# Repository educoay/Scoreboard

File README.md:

# Scoreboard
Arduino powered scoreboard with wired controller

**The wireless branch is newer and currently used in the application**

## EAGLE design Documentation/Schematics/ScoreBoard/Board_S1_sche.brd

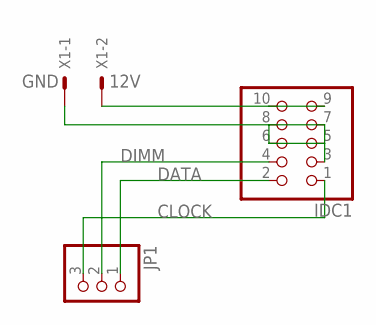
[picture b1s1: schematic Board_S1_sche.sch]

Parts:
IDC1: PINHD-2X5; 2X05
JP1: PINHD-1X3; 1X03
X1: KK-156-2

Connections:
12V: IDC1.9, IDC1.10, X1.2
CLOCK: IDC1.1, JP1.3
DATA: IDC1.2, JP1.1
DIMM: IDC1.4, JP1.2
GND: IDC1.3, IDC1.5, IDC1.6, IDC1.7, IDC1.8, X1.1

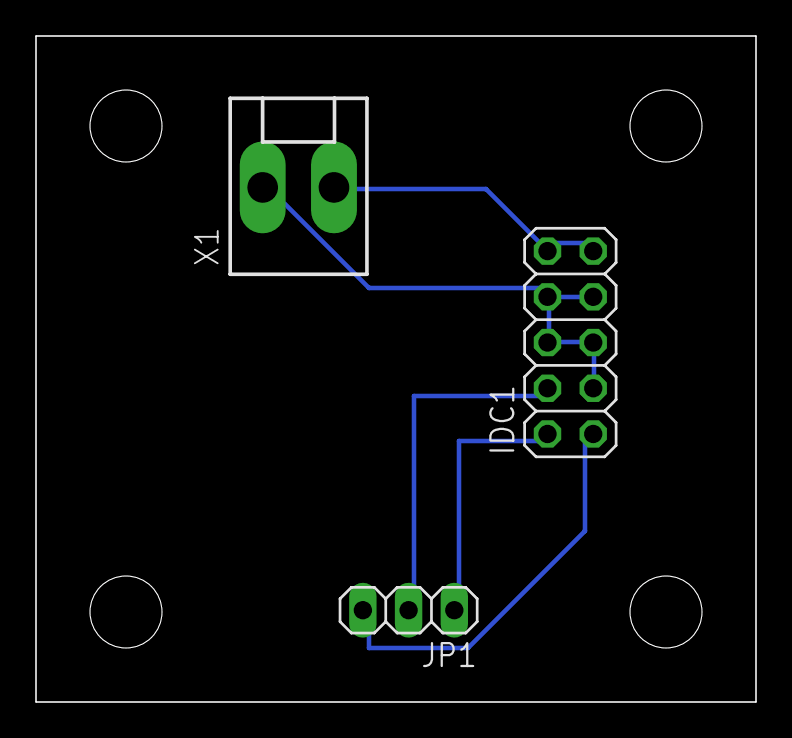
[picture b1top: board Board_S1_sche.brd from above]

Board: 2 copper layers, 40.0 x 37.0 mm, 3 parts (0 on the bottom side), 5 nets.

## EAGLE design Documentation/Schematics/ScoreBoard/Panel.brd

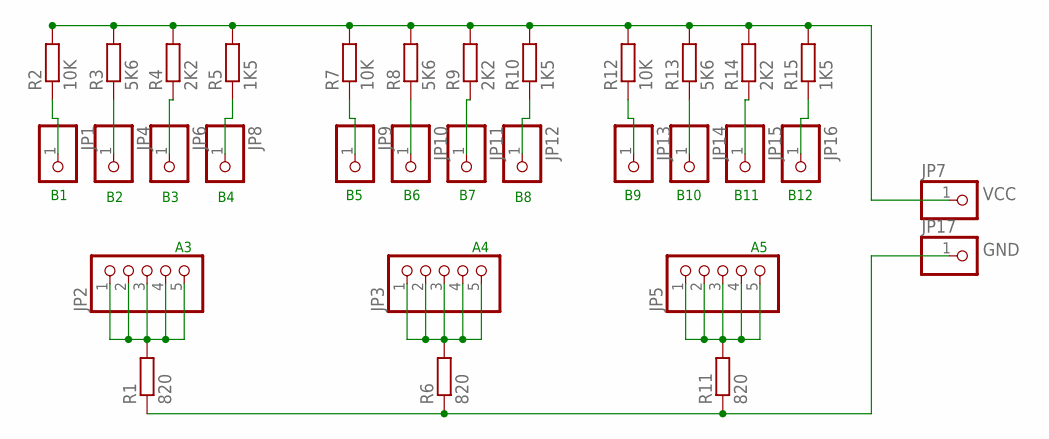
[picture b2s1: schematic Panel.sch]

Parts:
JP1, JP4, JP6, JP7, JP8, JP9, JP10, JP11, JP12, JP13, JP14, JP15, JP16, JP17: PINHD-1X1; 1X01
JP2, JP3, JP5: PINHD-1X5; 1X05
R1, R6, R11: 820; 0207/12
R2, R7, R12: 10K; 0207/12
R3, R8, R13: 5K6; 0207/12
R4, R9, R14: 2K2; 0207/12
R5, R10, R15: 1K5; 0207/12

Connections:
A1: JP3.1, JP3.2, JP3.3, JP3.4, JP3.5, R6.2
A2: JP5.1, JP5.2, JP5.3, JP5.4, JP5.5, R11.2
A3: JP2.1, JP2.2, JP2.3, JP2.4, JP2.5, R1.2
B1: JP1.1, R2.1
B2: JP4.1, R3.1
B3: JP6.1, R4.1
B4: JP8.1, R5.1
B5: JP9.1, R7.1
B6: JP10.1, R8.1
B7: JP11.1, R9.1
B8: JP12.1, R10.1
B9: JP13.1, R12.1
B10: JP14.1, R13.1
B11: JP15.1, R14.1
B12: JP16.1, R15.1
GND: JP17.1, R1.1, R6.1, R11.1
VCC: JP7.1, R2.2, R3.2, R4.2, R5.2, R7.2, R8.2, R9.2, R10.2, R12.2, R13.2, R14.2, R15.2

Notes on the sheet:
B10
B11
B12

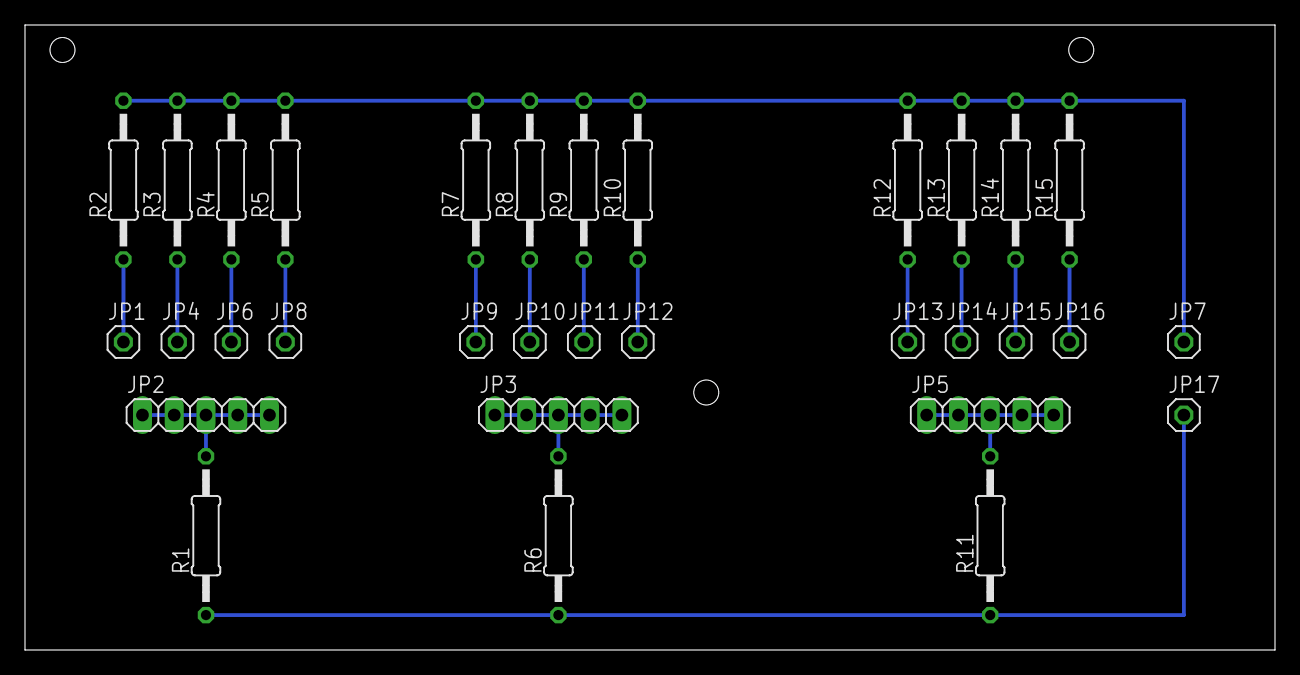
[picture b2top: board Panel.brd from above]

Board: 2 copper layers, 100.0 x 50.0 mm, 32 parts (0 on the bottom side), 17 nets.

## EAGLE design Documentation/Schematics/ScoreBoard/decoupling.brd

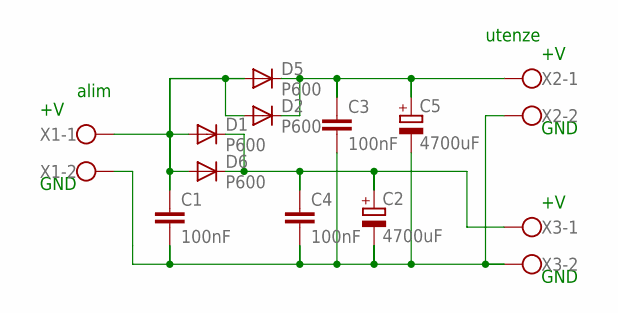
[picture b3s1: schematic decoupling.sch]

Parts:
C1, C3, C4: 100nF; C050-025X075
C2, C5: 4700uF; E7,5-16
D1, D2, D5, D6: P600; P6-15
X1, X2, X3: W237-102

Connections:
unnamed: C1.2, C2.-, C3.2, C4.2, C5.-, X1.2, X2.2, X3.2
unnamed: C1.1, D1.A, D2.A, D5.A, D6.A, X1.1
unnamed: C2.+, C4.1, D1.C, D6.C, X3.1
unnamed: C3.1, C5.+, D2.C, D5.C, X2.1

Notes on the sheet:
alim
utenze
GND

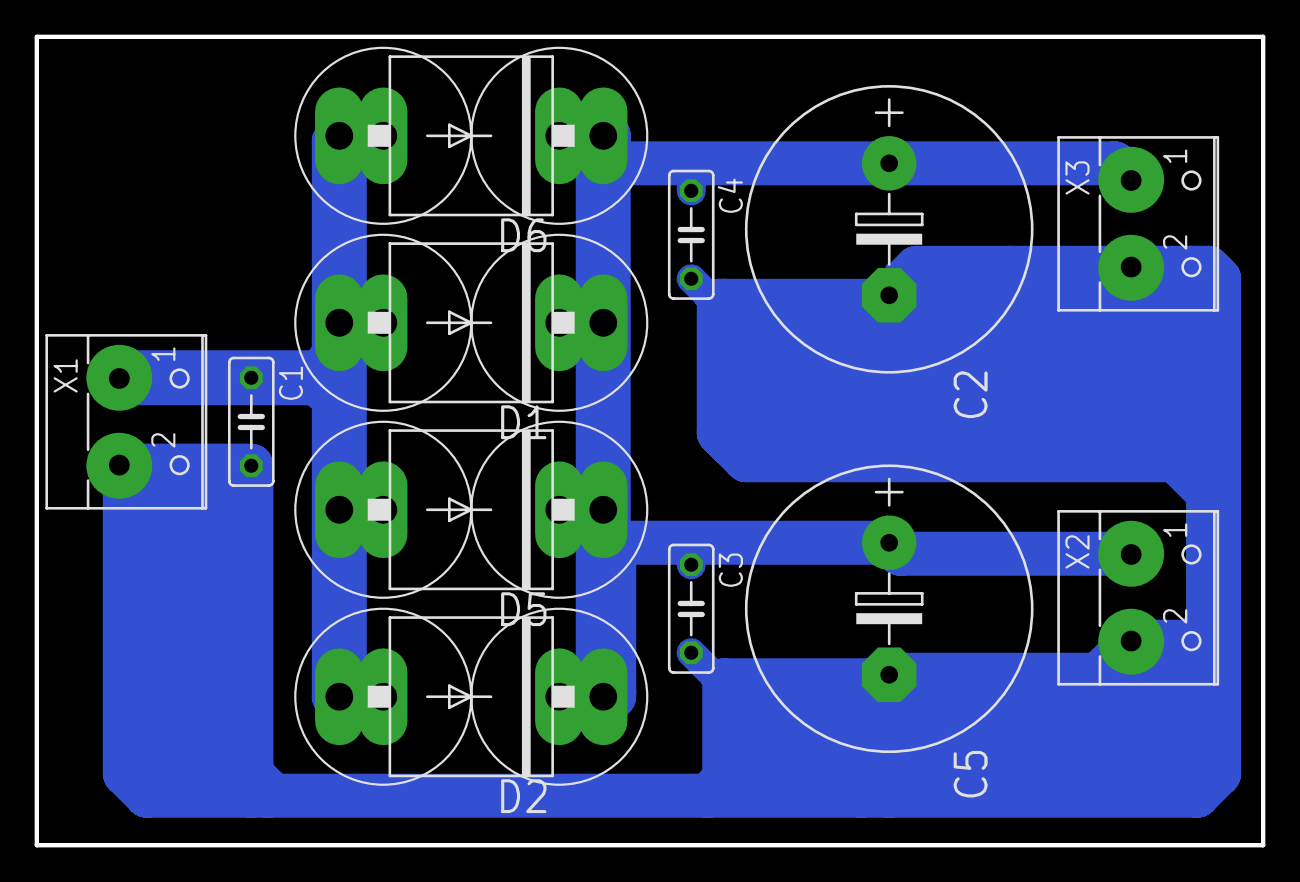
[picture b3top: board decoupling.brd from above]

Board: 2 copper layers, 70.8 x 46.7 mm, 12 parts (0 on the bottom side), 4 nets.

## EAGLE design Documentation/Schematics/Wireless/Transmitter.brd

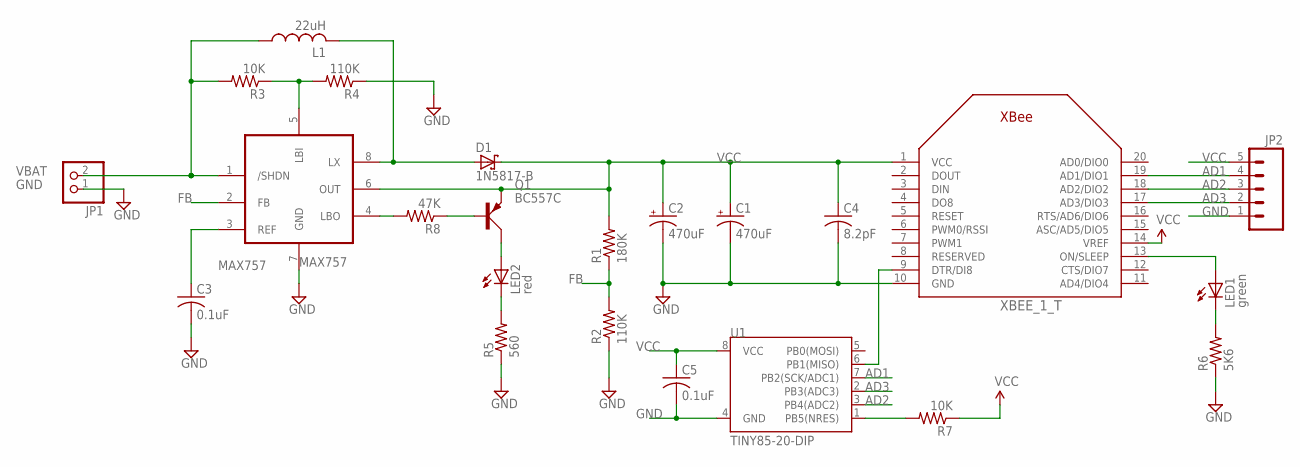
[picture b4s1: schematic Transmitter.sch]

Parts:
C1, C2: 470uF; E3,5-8
C3, C5: 0.1uF; C025-024X044
C4: 8.2pF; C025-024X044
D1: 1N5817-B; DO41-7.6
JP1: PINHD-1X2; 1X02
JP2: M05PTH; 1X05
L1: 22uH; 22R223C
LED1: green; LED3MM
LED2: red; LED3MM
MAX757: MAX757; DIL08
Q1: BC557C; TO92D
R1: 180K; 0207/10
R2, R4: 110K; 0207/10
R3, R7: 10K; 0207/10
R5: 560; 0207/10
R6: 5K6; 0207/10
R8: 47K; 0207/10
U1: TINY85-20-DIP; DIP08
XBEE_1_T: XBEE

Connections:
AD1: JP2.4, U1.7 (PB2(SCK/ADC1)), XBEE_1_T.19 (AD1/DIO1)
AD2: JP2.3, U1.3 (PB4(ADC2)), XBEE_1_T.18 (AD2/DIO2)
AD3: JP2.2, U1.2 (PB3(ADC3)), XBEE_1_T.17 (AD3/DIO3)
FB: MAX757.2 (FB), R1.1, R2.2
GND: C1.-, C2.-, C3.2, C4.2, C5.2, JP1.1, JP2.1, MAX757.7 (GND), R2.1, R4.1, R5.1, R6.1, U1.4 (GND), XBEE_1_T.10 (GND)
unnamed: U1.6 (PB1(MISO)), XBEE_1_T.9 (DTR/DI8)
unnamed: MAX757.4 (LBO), R8.2
unnamed: LED2.K (C), R5.2
unnamed: LED1.A, XBEE_1_T.13 (ON/SLEEP)
unnamed: LED1.K (C), R6.2
unnamed: MAX757.5 (LBI), R3.1, R4.2
unnamed: D1.A, L1.P$2 (2), MAX757.8 (LX)
unnamed: C3.1, MAX757.3 (REF)
unnamed: Q1.B, R8.1
unnamed: R7.2, U1.1 (PB5(NRES))
unnamed: LED2.A, Q1.C
VBAT: JP1.2, L1.P$1 (1), MAX757.1 (/SHDN), R3.2
VCC: C1.+, C2.+, C4.1, C5.1, D1.C, JP2.5, MAX757.6 (OUT), Q1.E, R1.2, R7.1, U1.8 (VCC), XBEE_1_T.1 (VCC), XBEE_1_T.14 (VREF)

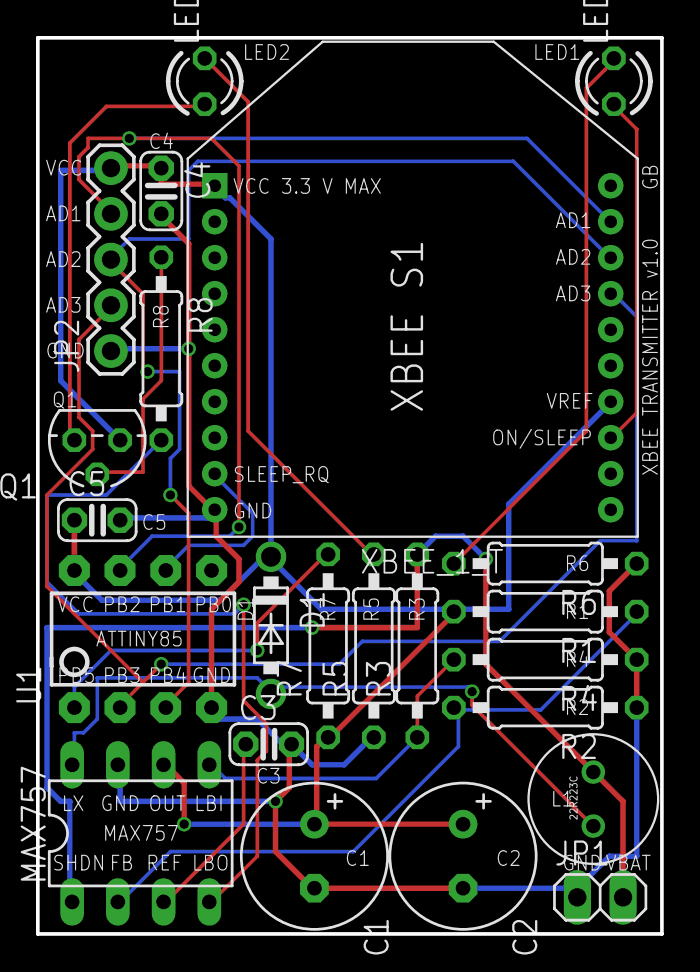
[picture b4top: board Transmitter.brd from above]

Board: 2 copper layers, 34.7 x 49.8 mm, 23 parts (0 on the bottom side), 18 nets.

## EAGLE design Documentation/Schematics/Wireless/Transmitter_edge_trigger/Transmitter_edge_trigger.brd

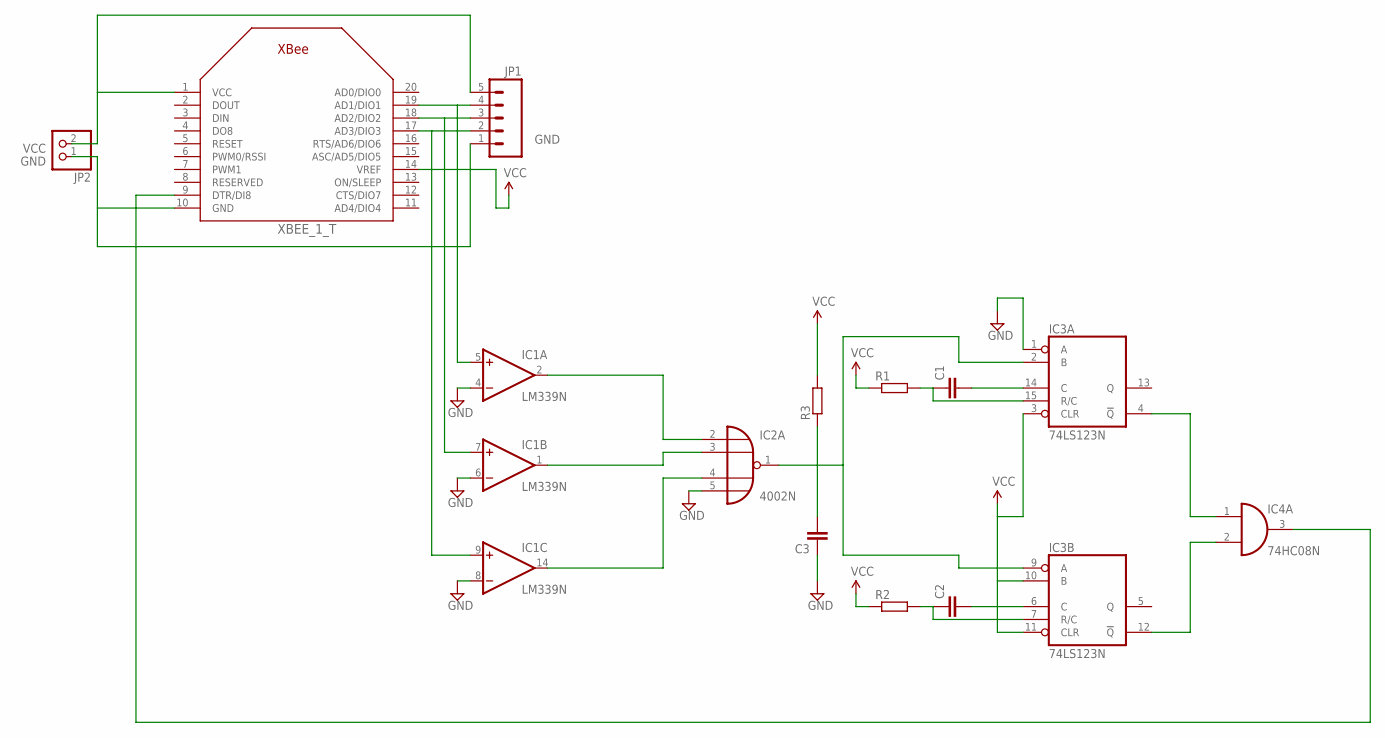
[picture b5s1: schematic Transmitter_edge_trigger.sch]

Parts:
C1, C2, C3: C-EU025-030X050; C025-030X050
IC1: LM339N; DIL14
IC2: 4002N; DIL14
IC3: 74LS123N; DIL16
IC4: 74HC08N; DIL14
JP1: M05PTH; 1X05
JP2: PINHD-1X2; 1X02
R1, R2, R3: R-EU_0207/12; 0207/12
XBEE_1_T: XBEE

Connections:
GND: C3.1, IC1.4 (-IN), IC1.6 (-IN), IC1.8 (-IN), IC1.12 (GND), IC2.5 (I3), IC3.1 (A), IC3.8 (GND), IC4.7 (GND), JP1.1, JP2.1, XBEE_1_T.10 (GND)
unnamed: IC1.5 (+IN), JP1.4, XBEE_1_T.19 (AD1/DIO1)
unnamed: IC1.2 (OUT), IC2.2 (I0)
unnamed: IC1.1 (OUT), IC2.3 (I1)
unnamed: IC1.14 (OUT), IC2.4 (I2)
unnamed: C3.2, IC2.1 (O), IC3.2 (B), IC3.9 (A), R3.1
unnamed: C1.2, IC3.14 (C)
unnamed: C1.1, IC3.15 (R/C), R1.2
unnamed: C2.1, IC3.7 (R/C), R2.2
unnamed: C2.2, IC3.6 (C)
unnamed: IC3.4 (!Q), IC4.1 (I0)
unnamed: IC3.12 (!Q), IC4.2 (I1)
unnamed: IC4.3 (O), XBEE_1_T.9 (DTR/DI8)
unnamed: IC1.9 (+IN), JP1.2, XBEE_1_T.17 (AD3/DIO3)
unnamed: IC1.7 (+IN), JP1.3, XBEE_1_T.18 (AD2/DIO2)
V+: IC1.3 (V+)
VCC: IC3.3 (CLR), IC3.10 (B), IC3.11 (CLR), IC3.16 (VCC), IC4.14 (VCC), JP1.5, JP2.2, R1.1, R2.1, R3.2, XBEE_1_T.1 (VCC), XBEE_1_T.14 (VREF)
VDD: IC2.14 (VDD)
VSS: IC2.7 (VSS)

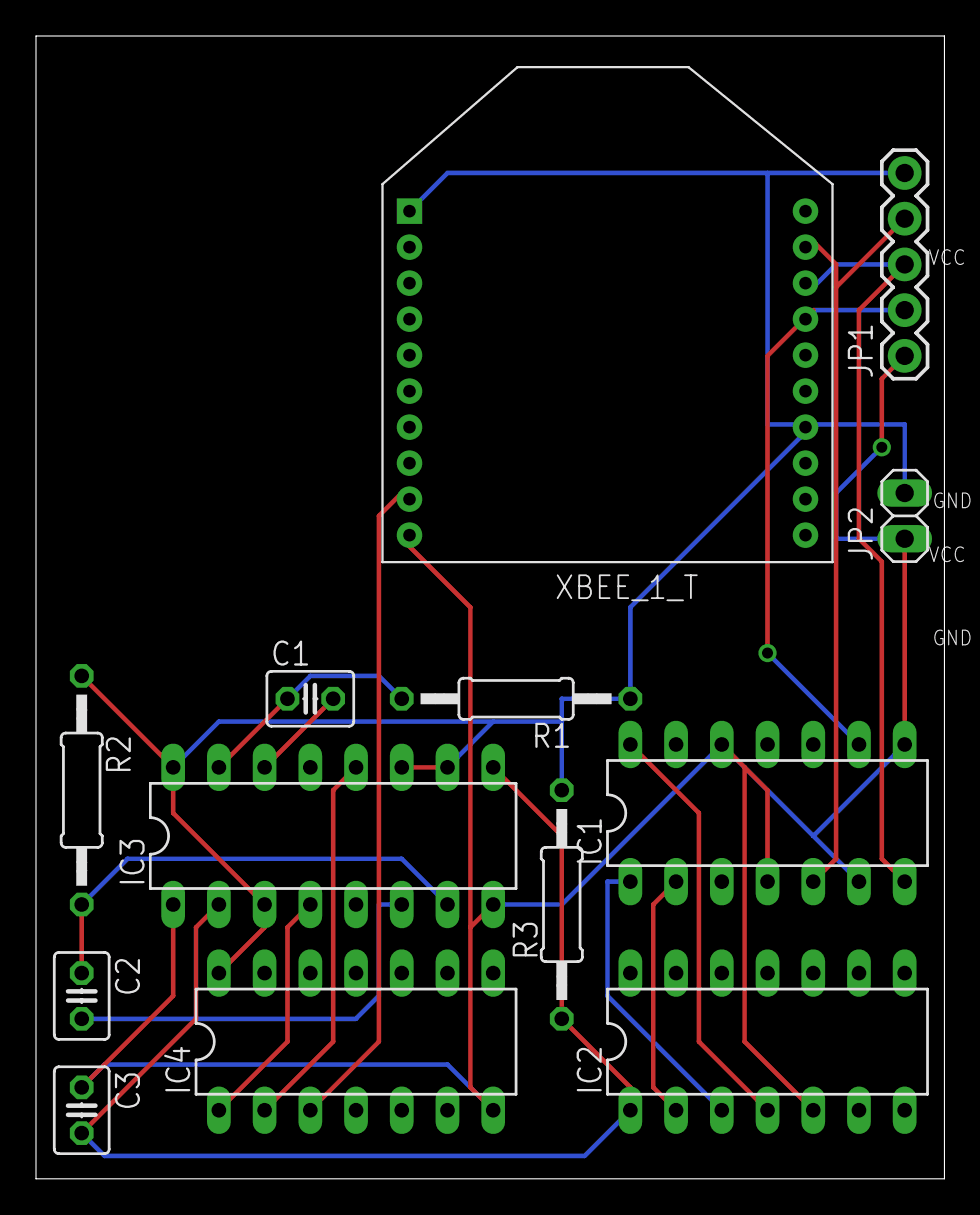
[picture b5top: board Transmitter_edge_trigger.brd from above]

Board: 2 copper layers, 50.5 x 63.5 mm, 13 parts (0 on the bottom side), 16 nets.

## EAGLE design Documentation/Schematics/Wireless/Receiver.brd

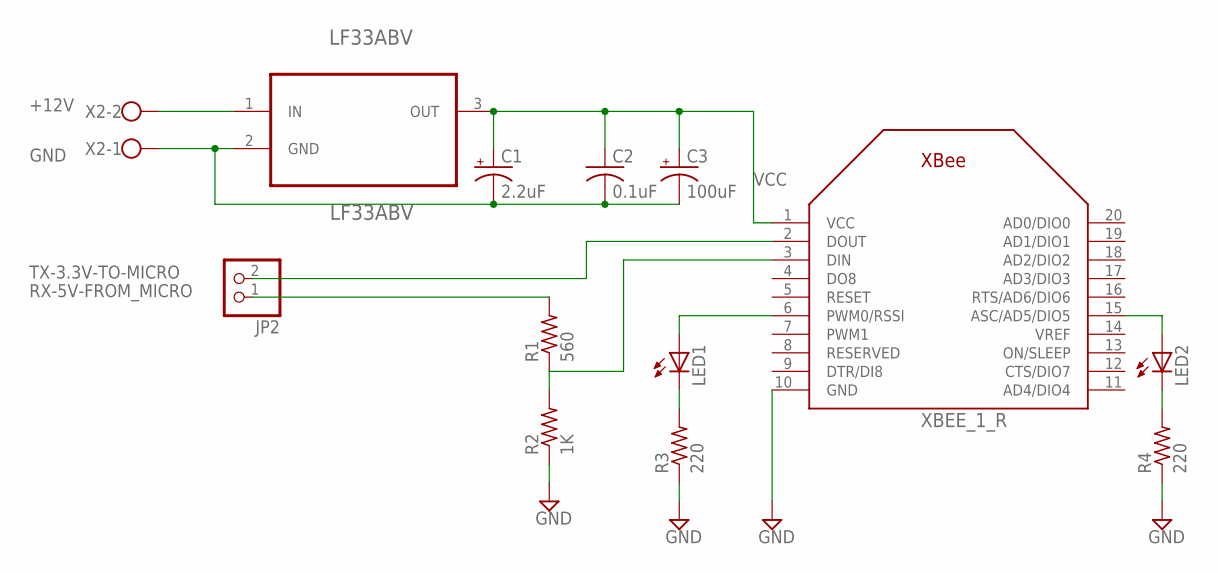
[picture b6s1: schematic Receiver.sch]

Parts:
C1: 2.2uF; CPOL-RADIAL-10UF-25V
C2: 0.1uF; C025-024X044
C3: 100uF; CPOL-RADIAL-100UF-25V
JP2: PINHD-1X2; 1X02
LED1, LED2: LED5MM
LF33ABV: LF33ABV; TO254P450X1020X1935-3P
R1: 560; 0207/10
R2: 1K; 0207/10
R3, R4: 220; 0207/10
X2: W237-102
XBEE_1_R: XBEE

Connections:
+12V: LF33ABV.1 (IN), X2.2
GND: C1.2 (-), C2.2, C3.2 (-), LF33ABV.2 (GND), R2.1, R3.1, R4.1, X2.1, XBEE_1_R.10 (GND)
unnamed: R1.1, R2.2, XBEE_1_R.3 (DIN)
unnamed: LED1.K (C), R3.2
unnamed: LED2.A, XBEE_1_R.15 (ASC/AD5/DIO5)
unnamed: LED2.K (C), R4.2
unnamed: LED1.A, XBEE_1_R.6 (PWM0/RSSI)
RX-5V-FROM_MICRO: JP2.1, R1.2
TX-3.3V-TO-MICRO: JP2.2, XBEE_1_R.2 (DOUT)
VCC: C1.1 (+), C2.1, C3.1 (+), LF33ABV.3 (OUT), XBEE_1_R.1 (VCC)

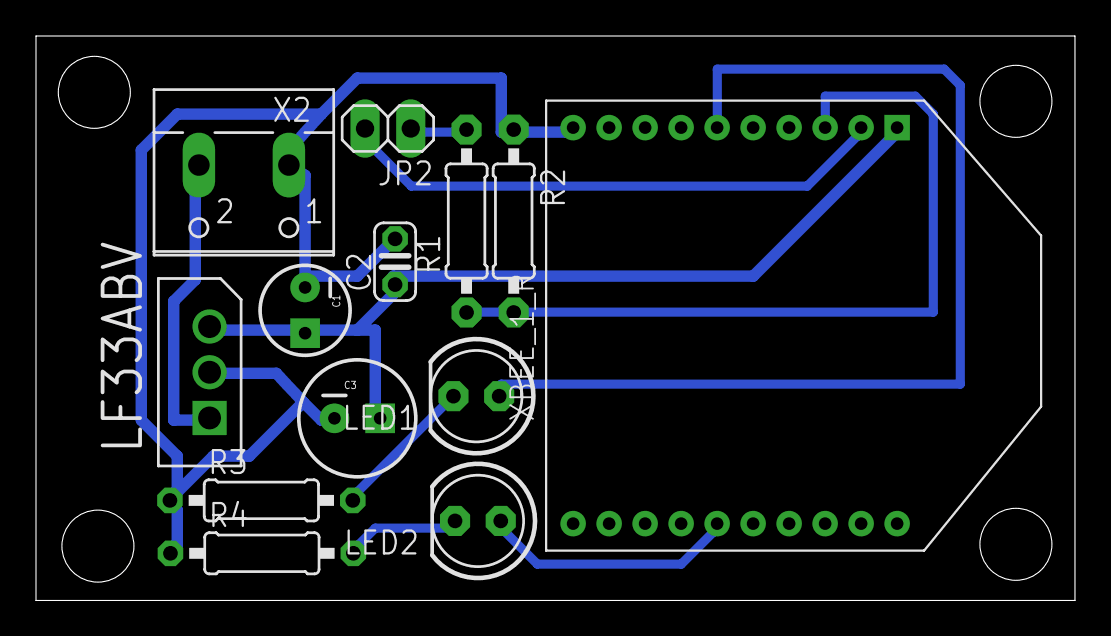
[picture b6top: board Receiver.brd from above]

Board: 2 copper layers, 57.7 x 31.4 mm, 13 parts (0 on the bottom side), 10 nets.

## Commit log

2015-01-25 Initial import of Eclispe projects: to read analog buttons, manage 7-seg displays and the main application
2015-01-25 Change in README for this main branch (wired)
2015-01-25 Added .gitignore
2015-01-25 Change in README for Markdown language
2015-01-25 Renamend projects in wireless branch
2015-01-25 Rename folders in wireless branch
2015-01-25 Updates of wireless branch from existing code. Version 1.0.0 with data recover on Arduino reset.
2015-01-25 Pull from origin/master to update readme
2015-01-25 Initial import of Xbee controller project: AVR ATTiny85U code to wake and sleep the Xbee. Eclispe project.
2015-01-25 Initial import of SoftwareSerial project, formerly NewSoftwareSerial from Arduino libraries. Eclispe project.
2015-01-25 Rename project
2015-01-25 Rename project folder
2015-01-25 Update readme with branch reference
2015-02-06 Added include directories for some symbols
2015-02-06 Version 1.0.0
2015-11-08 Removed SoftwareSerial directory (moved to util as a general purpose library), added Documentation folder with datasheets, schematics, bill of materials...
2015-11-08 Modified path to SoftwareSerial in makefile for main.cpp
2015-11-08 Added Documentation folder, only some file as a test
2015-11-08 Added scoreboard and control panel drafts in Doc folder
2015-11-08 Added grapichs and schematics in Doc folder
2015-11-08 Added datasheet of components in Doc folder
2015-11-29 Removed wrong project reference in Eclispe
2016-12-18 Reorganization of cores and library: changed projects includes and link folder. Removed library since they will move to a different repo.
2016-12-19 Update makefile with new path and libraries
2016-12-19 Update makefile with new path and libraries. Deleted old AnalogButtons library.
2016-12-20 Updated project path, changed AnalogButtons library with general version: the analog value is passed to the checkValue() function, to avoid reference to the analogRead() in the library.
2017-12-09 Updated project references to comply with new project names.
2018-04-30 Moved some components datasheet into new repo
2018-11-14 Added bill pdf
2018-11-14 Added bill pdfs

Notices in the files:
parts and their libraries:
SparkFun-Capacitors: Licensing: Creative Commons ShareAlike 4.0 International - https://creativecommons.org/licenses/by-sa/4.0
